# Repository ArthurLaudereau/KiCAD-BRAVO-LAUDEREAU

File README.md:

# Project Title

Clément BRAVO & Arthur LAUDEREAU 's KiCAD gas sensor project

### The project step by step

Firstly we creted a project using the Arduino UNO template on KiCAD.

Then, we created a symbol for each component : 
    - RN2483_Breakout
    - LTC1050
    - Gas sensor TO-5-4

And their footprints.

```
NOTE : We used a 8-pins connector to replace the RN2483_Breakout because it was too big,
but the footprint created is still in the library "projet" located in the folder
```

After the designing of the electrical schema

And assigning a footprint to each component,

We did the wiring on the PCB :

And to finish our "Piste Verte", we rendered our PCB in 3D !

## Bonus 

There is a backup of the wiring named "avant_remplissage", although it is not used
we decided to keep it to be safe.

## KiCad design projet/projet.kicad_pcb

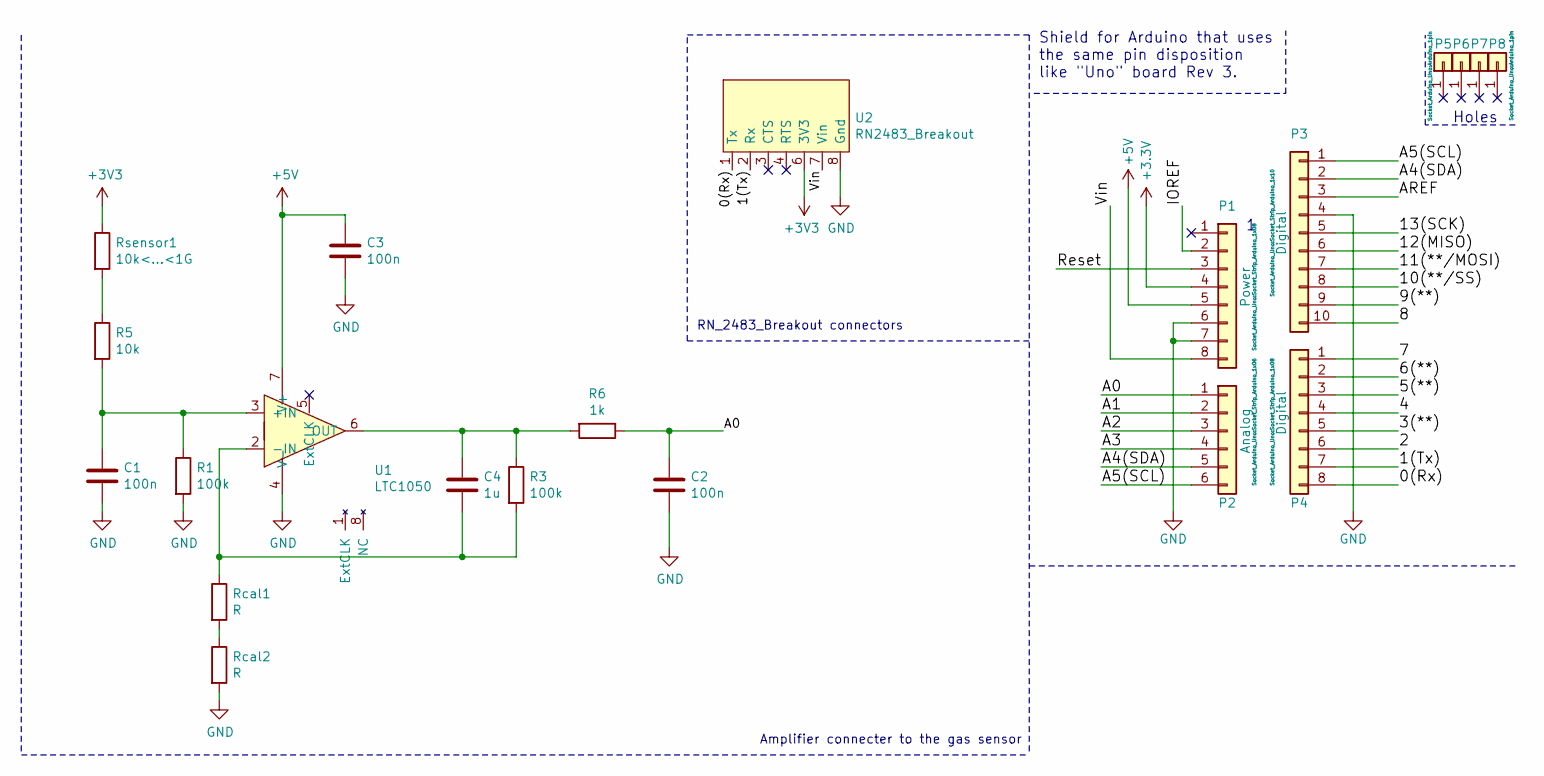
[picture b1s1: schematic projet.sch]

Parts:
C1, C2, C3: 100n; CP_Axial_L10.0mm_D4.5mm_P15.00mm_Horizontal
C4: 1u; CP_Axial_L10.0mm_D4.5mm_P15.00mm_Horizontal
P1: Power; Socket_Strip_Arduino_1x08
P2: Analog; Socket_Strip_Arduino_1x06
P3: Digital; Socket_Strip_Arduino_1x10
P4: Digital; Socket_Strip_Arduino_1x08
P5, P6, P7, P8: CONN_01X01; Arduino_1pin
R1, R3: 100k; R_Axial_DIN0204_L3.6mm_D1.6mm_P1.90mm_Vertical
R5: 10k; R_Axial_DIN0204_L3.6mm_D1.6mm_P1.90mm_Vertical
R6: 1k; R_Axial_DIN0204_L3.6mm_D1.6mm_P1.90mm_Vertical
Rcal1, Rcal2: R; R_Axial_DIN0204_L3.6mm_D1.6mm_P1.90mm_Vertical
Rsensor1: 10k<...<1G; TO-5-4
U1: LTC1050; DIP-8_W7.62mm_LongPads
U2: RN2483_Breakout

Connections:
+5V: C3.1, P1.5, U1.7 (V+)
/0(Rx): P4.8, U2.1 (Tx)
/1(Tx): P4.7, U2.2 (Rx)
/2: P4.6
/3(**): P4.5
/4: P4.4
/5(**): P4.3
/6(**): P4.2
/7: P4.1
/8: P3.10
/9(**): P3.9
/10(**/SS): P3.8
/11(**/MOSI): P3.7
/12(MISO): P3.6
/13(SCK): P3.5
/A0: C2.1, P2.1, R6.1
/A1: P2.2
/A2: P2.3
/A3: P2.4
/A4(SDA): P2.5, P3.2
/A5(SCL): P2.6, P3.1
/AREF: P3.3
/IOREF: P1.2
/Reset: P1.3
/Vin: P1.8, U2.7 (Vin)
GND: C1.2, C2.2, C3.2, P1.6, P1.7, P3.4, R1.2, Rcal2.2, U1.4 (V-), U2.8 (Gnd)
unnamed: C1.1, R1.1, R5.2, U1.3 (+IN)
unnamed: C4.1, R3.1, R6.2, U1.6 (OUT)
unnamed: C4.2, R3.2, Rcal1.1, U1.2 (-IN)
unnamed: R5.1, Rsensor1.2
unnamed: Rcal1.2, Rcal2.1

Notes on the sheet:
Holes
Shield for Arduino that uses the same pin disposition like "Uno" board Rev 3.
RN_2483_Breakout connectors
Amplifier connecter to the gas sensor

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
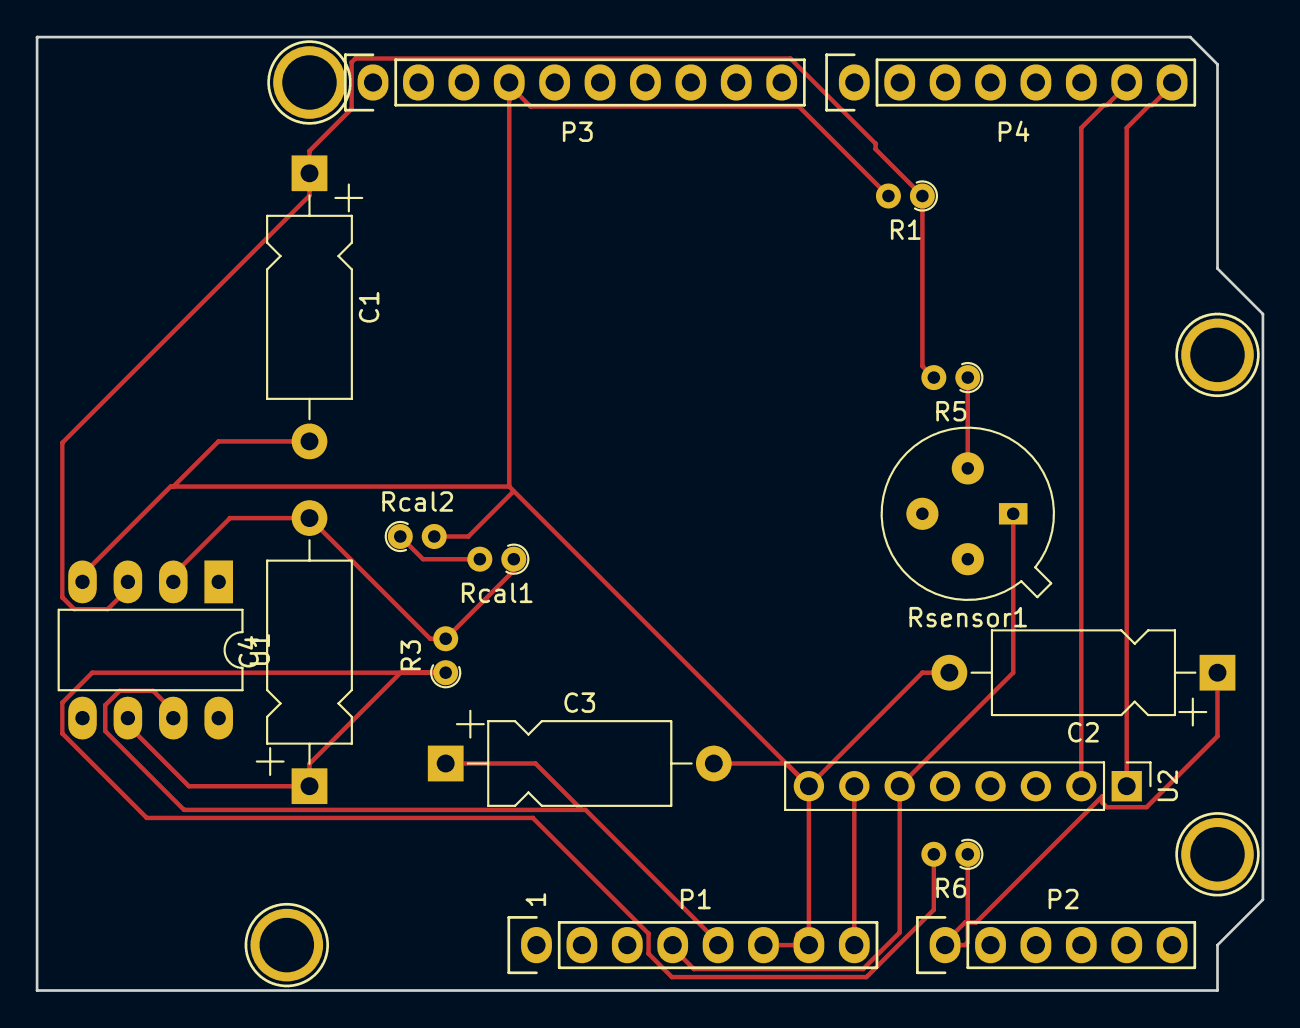
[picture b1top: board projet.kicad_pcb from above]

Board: 2 copper layers, 68.6 x 53.3 mm, 21 parts (0 on the bottom side), 14 nets.

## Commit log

2018-11-28 Readme update
